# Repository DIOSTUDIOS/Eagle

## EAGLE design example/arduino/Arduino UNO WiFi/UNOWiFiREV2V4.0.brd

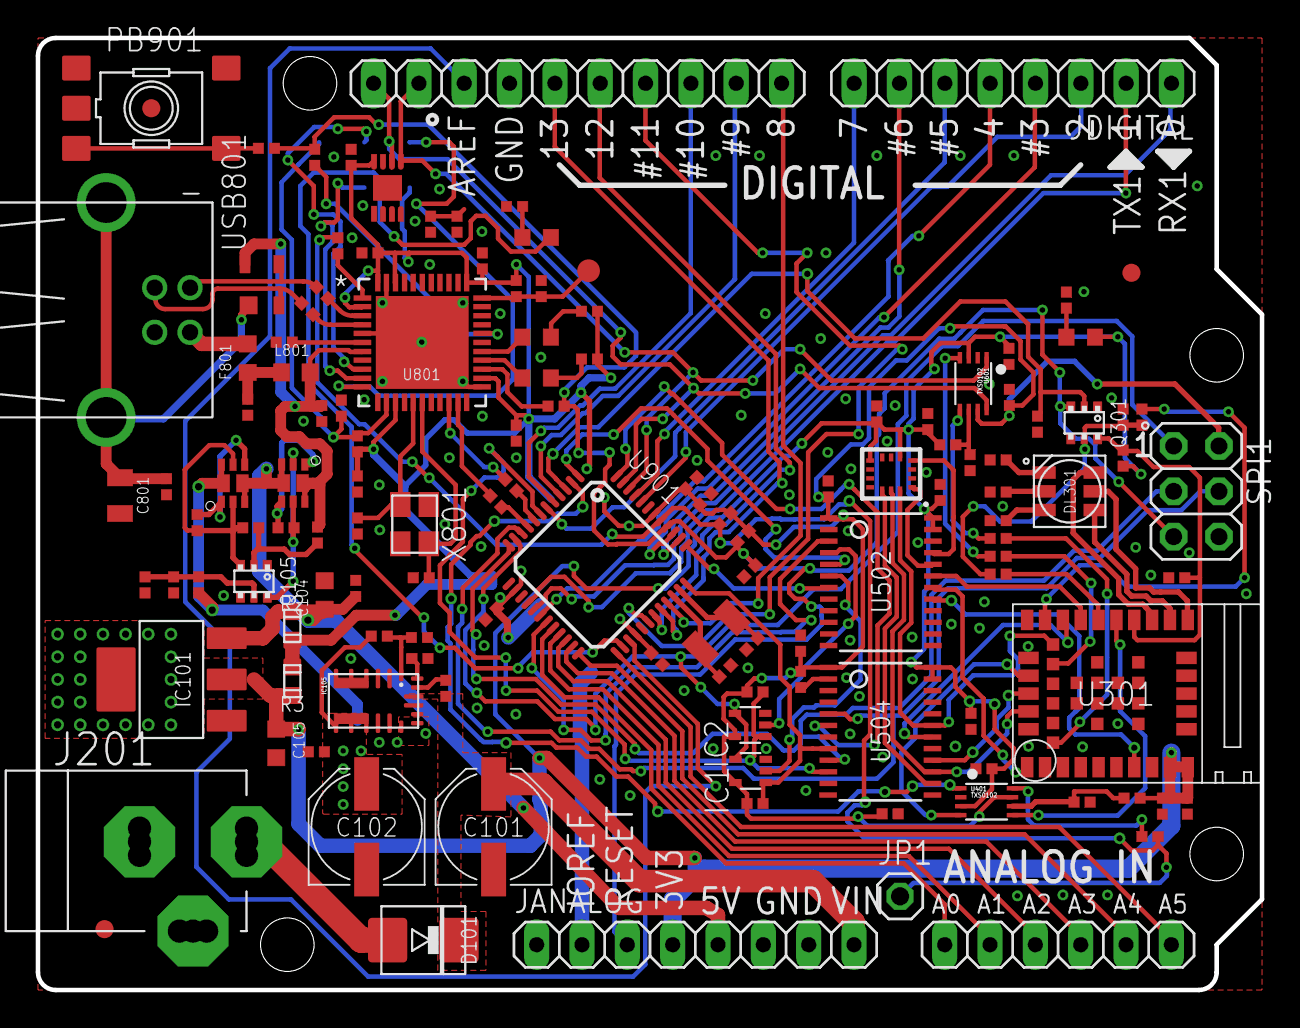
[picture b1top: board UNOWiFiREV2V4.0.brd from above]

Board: 2 copper layers, 68.6 x 53.3 mm, 145 parts (1 on the bottom side), 117 nets.

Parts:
C1, C103, C106, C114, C201, C202, C301, C302, C303, C401, C402, C403, C503, C504, C505, C506, C601, C602, C603, C701, C805, C806, C807, C808, C809, C902, C903, C906, C907: 100n; 0402-1005X55N
C2, C901: 4u7; 0402-1005X55N
C101, C102: 47u; PANASONIC_D
C104, C105: 10u; 0603-1608X90N
C801: 4n7; 0805-R2013X50N
C802, C803: 1n; 0402-1005X55N
C804: 1u; 0402-1005X55N
C810, C811: 12pF; 0402-1005X55N
C904, C905: 20p; 0402-1005X55N
D101: 1N4007; SMB_DO214AA
D801: PRTR5V; SOT190P230X110-4N
DL301: RGB; RGBLED
F801: 0.5A; 0603-1608X90N
FD1, FD2, FD3: DNP; FD-1-2
FRAME1, FRAME101, FRAME201, FRAME301, FRAME401, FRAME501, FRAME601, FRAME701, FRAME801, FRAME901: DNP; FRAME
GND800: DNP; TP-1.00MM
HOLDER: HOLDER-UNOWIFI; HOLDER
IC1, IC2: 74LVC1G125DCKR; SC70-5
IC101: -; SOT223
IC105: MPM3610
J201: -; POWERSUPPLY_DC-21MM
JANALOG: -; 1X14_
JDIGITAL: -; 1X18_
JP1: 1X01
L801: BLM18PG471; 0603-1608X90N
LRX800: YELLOW; LEDC1608X80N-AK
LTX800: YELLOW; LEDC1608X80N-AK
MISO800: DNP; TP-1.00MM
MOSI800: DNP; TP-1.00MM
ON100: GREEN; LEDC1608X80N-AK
PB901: -; TS42
Q101, Q102: DMP2160; PWR_SC70
Q105, Q301: BSS138PS; SOT363
R1, R804, R805, R807, R808: 1k; 0402-1005X55N
R2: 0R; C0603
R3: DNP; C0603
R4, R303, R304, R310, R806: 0R; 0402-1005X55N
R5, R11, R102, R123, R124, R125, R130, R301, R302, R308, R405, R504, R605, R803, R809, R902: 100k; 0402-1005X55N
R101, R126, R305, R306, R307, R802, R903: 330R; 0402-1005X55N
R127, R128: 10k; 0402-1005X55N
R129: 19k1; 0402-1005X55N
R131: 53k6; 0402-1005X55N
R309, R810, R901: DNP; 0402-1005X55N
R801: 1M; 0402-1005X55N
R811, R812: 22R; 0402-1005X55N
R904: 39R; 0402-1005X55N
RST800: DNP; TP-1.00MM
SCK800: DNP; TP-1.00MM
SPI1: -; 2X03
TP801: DNP; TP-1.27MM
U201: LSM6DS3TR; LGA14L
U301: NINA-W132; NINA-W1X
U401, U601: TXS0102; VFSOP-8
U502, U504: MC74LVX4245; TSSOP24
U701: ECC608; SON50P300X200X60-9N-EP160X140
U801: ATMEGA32U4RC; QFN50P700X700X100-45N
U901: ATMEGA4809; TQFP48
USB801: -; USB-B-H
USR: YELLOW; LEDC1608X80N-AK
VDD800: DNP; TP-1.00MM
X801: 16MHz; CRYSTAL-3.2-2.5
Y901: 32768Hz; ABS07

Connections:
2XTRANSLATOR1:N$1: C601.1, R605.1, U601.P$6
2XTRANSLATOR2:N$1: C401.1, R405.1, U401.P$6
16XTRANSLATOR1:N$1: R504.1, U504.2
+3V3: C105.1, C201.1, C202.1, C301.1, C302.2, C402.1, C505.1, C506.1, C602.1, IC101.2, IC101.4, JANALOG.4, ON100.A, R3.1, R301.2, R405.2, R605.2, U201.5, U201.8, U301.9, U301.10, U401.P$3, U502.23, U502.24, U504.23, U504.24, U601.P$3
+5V: C104.1, C106.1, IC101.3, JANALOG.5, Q101.D2, Q101.D2', Q102.D2, Q102.D2', R2.1
GND: C1.2, C2.2, C101.-, C102.-, C103.2, C104.2, C105.2, C106.2, C114.2, C201.2, C202.2, C301.2, C302.1, C303.2, C401.2, C402.2, C403.2, C503.2, C504.2, C505.2, C506.2, C601.2, C602.2, C603.2, C701.1, C801.2, C802.2, C803.2, C804.2, C805.2, C806.2, C807.2, C808.1, C809.1, C810.2, C811.1, C901.2, C902.1, C903.2, C904.2, C905.2, C906.1, C907.1, GND800.X, IC1.3, IC2.3, IC101.1, IC105.3, IC105.12, IC105.13, IC105.14, J201.-1, J201.-2, J201.-3, J201.E1, J201.E2, J201.E3, JANALOG.6, JANALOG.7, JDIGITAL.15, PB901.1, PB901.2, PB901.5, Q105.1, Q105.4, Q301.1, Q301.4, R1.2, R101.2, R124.1, R129.1, R131.1, R302.2, R305.1, R306.1, R307.1, R308.2, R801.1, R810.1, SPI1.6, U201.2, U201.3, U201.6, U201.7, U301.6, U301.12, U301.14, U301.26, U301.30, U301.GND@1, U301.GND@2, U301.GND@3, U301.GND@4, U301.GND@5, U301.GND@6, U301.GND@7, U301.GND@8, U301.GND@9, U301.GND@10, U301.GND@11, U301.GND@12, U401.P$2, U502.2, U502.11, U502.12, U502.13, U502.14, U502.15, U502.16, U502.22, U504.3, U504.4, U504.7, U504.11, U504.12, U504.13, U504.22, U601.P$2, U701.4, U701.9, U801.5, U801.15, U801.23, U801.35, U801.43, U801.45, U901.15, U901.29, U901.43, USB801.GND, X801.2, X801.4
MEDBG1:N$1: C801.1, D801.1, R801.2, USB801.SHIELD1, USB801.SHIELD2
MEDBG1:N$2: F801.2, USB801.VBUS
MEDBG1:N$3: C802.1, F801.1, L801.1
MEDBG1:N$4: R802.1, U801.1
MEDBG1:N$5: C804.1, U801.6
MEDBG1:N$6: C805.1, R803.1, RST800.X, U801.13
MEDBG1:N$7: C811.2, U801.16, X801.1
MEDBG1:N$8: C810.1, U801.17, X801.3
MEDBG1:N$9: R804.2, U801.20
MEDBG1:N$10: R805.2, U801.21
MEDBG1:N$11: LTX800.C, U801.27
MEDBG1:N$12: R806.1, U801.25
MEDBG1:N$13: LRX800.C, U801.26
MEDBG1:N$14: LTX800.A, R808.1
MEDBG1:N$15: LRX800.A, R807.1
MEDBG1:N$16: R809.1, R810.2, TP801.X, U801.33
MEDBG1:N$17: MISO800.X, U801.11
MEDBG1:N$18: MOSI800.X, U801.10
MEDBG1:N$19: SCK800.X, U801.9
MEDBG1:USB2_N: R811.1, U801.3
MEDBG1:USB2_PI: R812.1, U801.4
MEDBG1:USB_N: D801.3, R811.2, USB801.D-
MEDBG1:USB_P: D801.2, R812.2, USB801.D+
unnamed: U301.20, U401.P$5
unnamed: U301.1, U502.18
unnamed: U301.22, U502.19
unnamed: U201.14, U301.36, U504.19
unnamed: U301.23, U504.18
unnamed: U201.1, U502.20
unnamed: U301.27, U401.P$4
unnamed: U301.28, U504.16
unnamed: IC1.2, U502.6
unnamed: IC2.2, U502.4
unnamed: R304.2, U601.P$5
unnamed: R303.2, U601.P$4
unnamed: JP1.1, R4.2, R802.2, R901.1, U901.41
unnamed: U201.4, U502.21
unnamed: U201.12, U504.14
unnamed: R903.2, U801.29
unnamed: U301.7, U502.17
unnamed: R805.1, U901.9
unnamed: R804.1, U901.8
unnamed: U901.26, USR.A
unnamed: R1.1, USR.C
unnamed: U201.13, U301.29, U504.15
PA0: JDIGITAL.3, U901.44
PA1: JDIGITAL.8, U901.45
PA2: JDIGITAL.17, U601.P$1, U701.5, U901.46
PA3: JDIGITAL.18, U601.P$8, U701.6, U901.47
PA4: U504.6, U901.48
PA5: U502.5, U901.1
PA6: U401.P$1, U901.2
PA7: Q301.2, R302.1, U901.3
PB0: JDIGITAL.10, U901.4
PB1: JDIGITAL.11, U901.5
PB2: JDIGITAL.6, U901.6
PB3: IC2.1, R5.1, U504.10, U901.7
PC0: SPI1.4, U504.5, U901.10
PC1: IC1.4, IC2.4, SPI1.1, U901.11
PC2: SPI1.3, U504.9, U901.12
PC4: JDIGITAL.2, U901.16
PC5: JDIGITAL.1, U901.17
PC6: JDIGITAL.5, U901.18
PC7: U502.3, U901.19
PD0: JANALOG.9, U901.20
PD1: JANALOG.10, U901.21
PD2: JANALOG.11, U901.22
PD3: JANALOG.12, U901.23
PD4: JANALOG.13, U901.24
PD5: JANALOG.14, U901.25
PD7: C1.1, C2.1, JDIGITAL.16, U901.27
PE0: JDIGITAL.12, U901.30
PE1: JDIGITAL.13, U901.31
PE2: JDIGITAL.14, U901.32
PE3: JDIGITAL.9, U901.33
PF2: IC1.1, R11.1, U504.8, U901.36
PF3: U502.7, U901.37
PF4: JDIGITAL.7, U901.38
PF5: JDIGITAL.4, U901.39
PWR1:N17690335: Q101.S1, Q101.S2, R127.2
PWR1:N17690346: Q101.G1, Q101.G2, Q105.6, R127.1
PWR1:N17690381: Q105.2, R125.1, R126.2
PWR1:N17690821: Q102.S1, Q102.S2, R128.2
PWR1:N17690840: Q102.G1, Q102.G2, Q105.3, R126.1, R128.1
PWR1:N17690878: C114.1, Q105.5, R123.1, R124.2
PWR1:N$1: D101.A, J201.+1, J201.+2, J201.+3
PWR1:N$3: C102.+, C103.1, IC105.7, IC105.8, IC105.9, IC105.20, Q102.D1, Q102.D1', R102.2, R123.2
PWR1:N$4: ON100.C, R101.1
PWR1:N$35: IC105.1, R102.1, R129.2
PWR1:N$36: IC105.17, R130.2
PWR1:N$37: IC105.18, R131.2
TRG_RST: C903.1, JANALOG.3, Q301.3, R806.2, R902.1, R903.1, R904.1, SPI1.5, U901.40
UC1:N$2: PB901.3, PB901.4, R904.2
UC1:N$3: C905.1, U901.34, Y901.1
UC1:N$4: C904.1, U901.35, Y901.2
UPDI_REMOTE: R4.1, U401.P$8
VDD: C403.1, C503.1, C504.1, C603.1, C701.2, C806.1, C807.1, C808.2, C809.2, C901.1, C902.2, C906.2, C907.2, IC1.5, IC2.5, JANALOG.2, R2.2, R3.2, R5.2, R11.2, R504.2, R803.2, R807.2, R808.2, R809.2, R901.2, R902.2, SPI1.2, U401.P$7, U502.1, U504.1, U601.P$7, U701.8, U801.2, U801.14, U801.24, U801.34, U801.42, U801.44, U901.14, U901.28, U901.42, VDD800.X
VIN: C101.+, D101.C, IC105.16, JANALOG.8, R130.1
VUSB: C803.1, D801.4, L801.2, Q101.D1, Q101.D1', R125.2, U801.7
WIFI/BLE1:N$1: C303.1, Q301.6, R301.1, U301.19
WIFI/BLE1:N$2: R303.1, U301.35
WIFI/BLE1:N$3: R304.1, U301.31
WIFI/BLE1:N$4: DL301.2, U301.16
WIFI/BLE1:N$5: DL301.1, U301.17
WIFI/BLE1:N$6: DL301.3, U301.18
WIFI/BLE1:N$7: DL301.5, R305.2
WIFI/BLE1:N$8: DL301.6, R306.2
WIFI/BLE1:N$9: DL301.4, R307.2
WIFI/BLE1:N$10: R309.2, U301.24
WIFI/BLE1:N$11: Q301.5, R308.1, R309.1, R310.1
WIFI/BLE1:N$12: R310.2, U301.21

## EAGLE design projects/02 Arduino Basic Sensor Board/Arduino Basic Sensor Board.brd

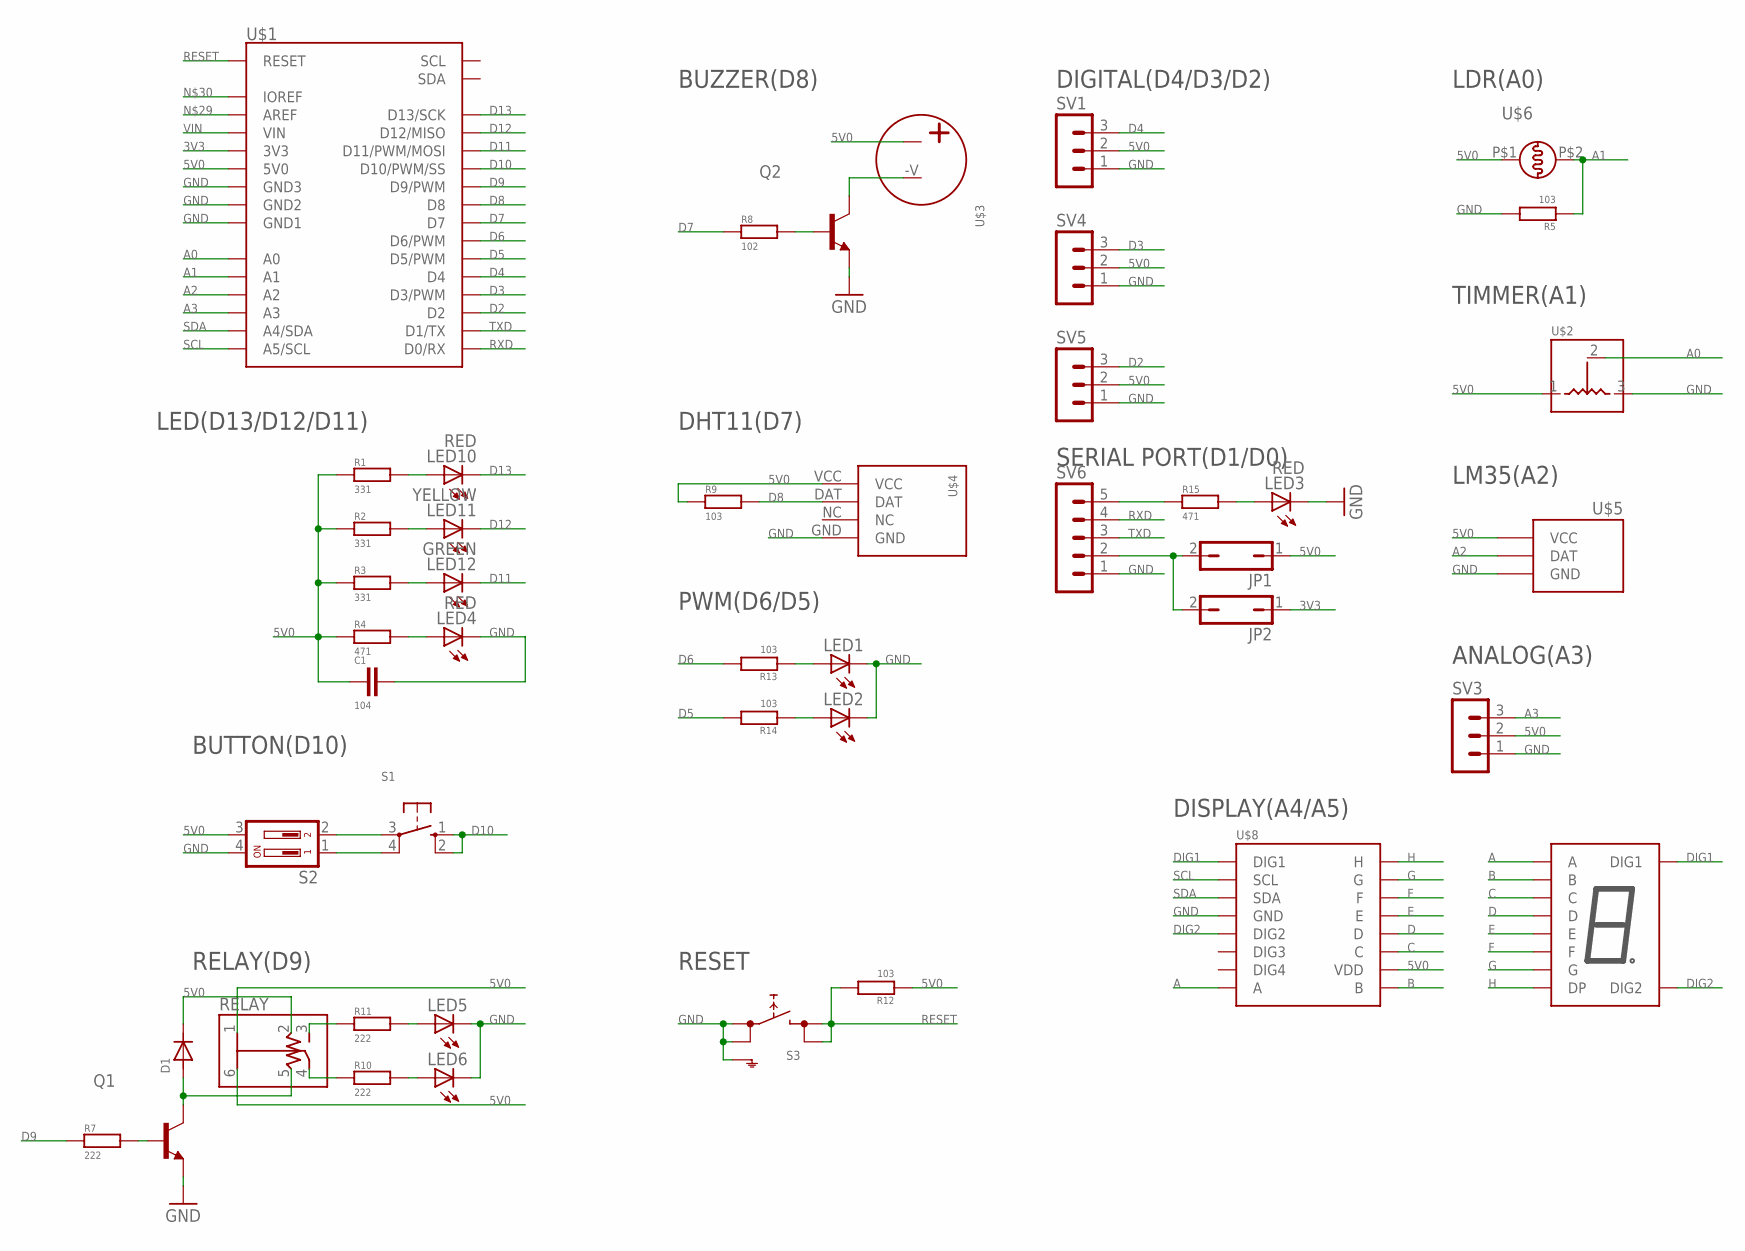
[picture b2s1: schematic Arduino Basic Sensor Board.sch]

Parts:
C1: 104; C0805
D1: DIODESMB; SMB
JP1, JP2: JP1Q
LED1, LED2: LEDCHIPLED_1206; LED1206
LED3, LED4: RED; LED0805
LED5, LED6: LEDSML1206; SML1206
LED10: RED; SML1206
LED11: YELLOW; SML1206
LED12: GREEN; SML1206
Q1, Q2: S8050SOT23; SOT23
R1, R2, R3: 331; R0805
R4, R15: 471; R0805
R5, R9, R12, R13, R14: 103; R0805
R7, R10, R11: 222; R0805
R8: 102; R0805
RELAY: RELAY-HK4100F-DC5V
S1: TS-DIP-4.54.5; TS-DIP-4.5*4.5
S2: SD4-02
S3: TS-SMD_6S6_SHIELD; TS-SMD_6*6_SHIELD
SV1, SV3, SV4, SV5: MA03-1
SV6: MA05-1
U$1: ARDUINO-UNO
U$2: 33623362; 3362
U$3: BUZZER
U$4: DHT11
U$5: LM35; TO92
U$6: LDR
U$8: TM1650; SOP16
U$15: 3261AS; TN_AS_2_0.36INCH

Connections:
3V3: JP2.1, U$1.3V3
5V0: C1.2, D1.1, JP1.1, R1.1, R2.1, R3.1, R4.1, R9.1, R12.1, RELAY.1, RELAY.2, RELAY.6, S2.3, SV1.2, SV3.2, SV4.2, SV5.2, U$1.5V0, U$2.1, U$3.+V, U$4.VCC, U$5.1 (VCC), U$6.P$1, U$8.10 (VDD)
A: U$8.8 (A), U$15.3 (A)
A0: U$1.A0, U$2.2
A1: R5.1, U$1.A1, U$6.P$2
A2: U$1.A2, U$5.2 (DAT)
A3: SV3.3, U$1.A3
B: U$8.9 (B), U$15.9 (B)
C: U$8.11 (C), U$15.8 (C)
D: U$8.12 (D), U$15.6 (D)
D2: SV5.3, U$1.D2
D3: SV4.3, U$1.D3 (D3/PWM)
D4: SV1.3, U$1.D4
D5: R14.2, U$1.D5 (D5/PWM)
D6: R13.2, U$1.D6 (D6/PWM)
D7: R8.1, U$1.D7
D8: R9.2, U$1.D8, U$4.DAT
D9: R7.1, U$1.D9 (D9/PWM)
D10: S1.1 (S), S1.2 (S1), U$1.D10 (D10/PWM/SS)
D11: LED12.C, U$1.D11 (D11/PWM/MOSI)
D12: LED11.C, U$1.D12 (D12/MISO)
D13: LED10.C, U$1.D13 (D13/SCK)
DIG1: U$8.1 (DIG1), U$15.10 (DIG1)
DIG2: U$8.5 (DIG2), U$15.5 (DIG2)
E: U$8.13 (E), U$15.7 (E)
F: U$8.14 (F), U$15.4 (F)
G: U$8.15 (G), U$15.1 (G)
GND: C1.1, LED1.C, LED2.C, LED3.C, LED4.C, LED5.C, LED6.C, Q1.E, Q2.E, R5.2, S2.4, S3.1 (1.1), S3.2 (1.2), S3.5 (SH), SV1.1, SV3.1, SV4.1, SV5.1, SV6.1, U$1.GND1, U$1.GND2, U$1.GND3, U$2.3, U$4.GND, U$5.3 (GND), U$8.4 (GND)
H: U$8.16 (H), U$15.2 (DP)
unnamed: LED10.A, R1.2
unnamed: LED11.A, R2.2
unnamed: LED12.A, R3.2
unnamed: LED4.A, R4.2
unnamed: S1.4 (P1), S2.1
unnamed: S1.3, S2.2
unnamed: LED1.A, R13.1
unnamed: R10.1, RELAY.4
unnamed: R11.1, RELAY.3
unnamed: LED6.A, R10.2
unnamed: LED5.A, R11.2
unnamed: LED2.A, R14.1
unnamed: JP1.2, JP2.2, SV6.2
unnamed: R15.1, SV6.5
unnamed: LED3.A, R15.2
unnamed: D1.2, Q1.C, RELAY.5
unnamed: Q1.B, R7.2
unnamed: Q2.B, R8.2
unnamed: Q2.C, U$3.-V
RESET: R12.2, S3.3 (2.1), S3.4 (2.2), U$1.RST (RESET)
RXD: SV6.4, U$1.D0 (D0/RX)
SCL: U$1.A5 (A5/SCL), U$8.2 (SCL)
SDA: U$1.A4 (A4/SDA), U$8.3 (SDA)
TXD: SV6.3, U$1.D1 (D1/TX)
VIN: U$1.VIN

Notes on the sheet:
LED(D13/D12/D11)
BUTTON(D10)
RELAY(D9)
SERIAL PORT(D1/D0)
DHT11(D7)
BUZZER(D8)
ANALOG(A3)
LM35(A2)
TIMMER(A1)
LDR(A0)
PWM(D6/D5)
DIGITAL(D4/D3/D2)
RESET
DISPLAY(A4/A5)

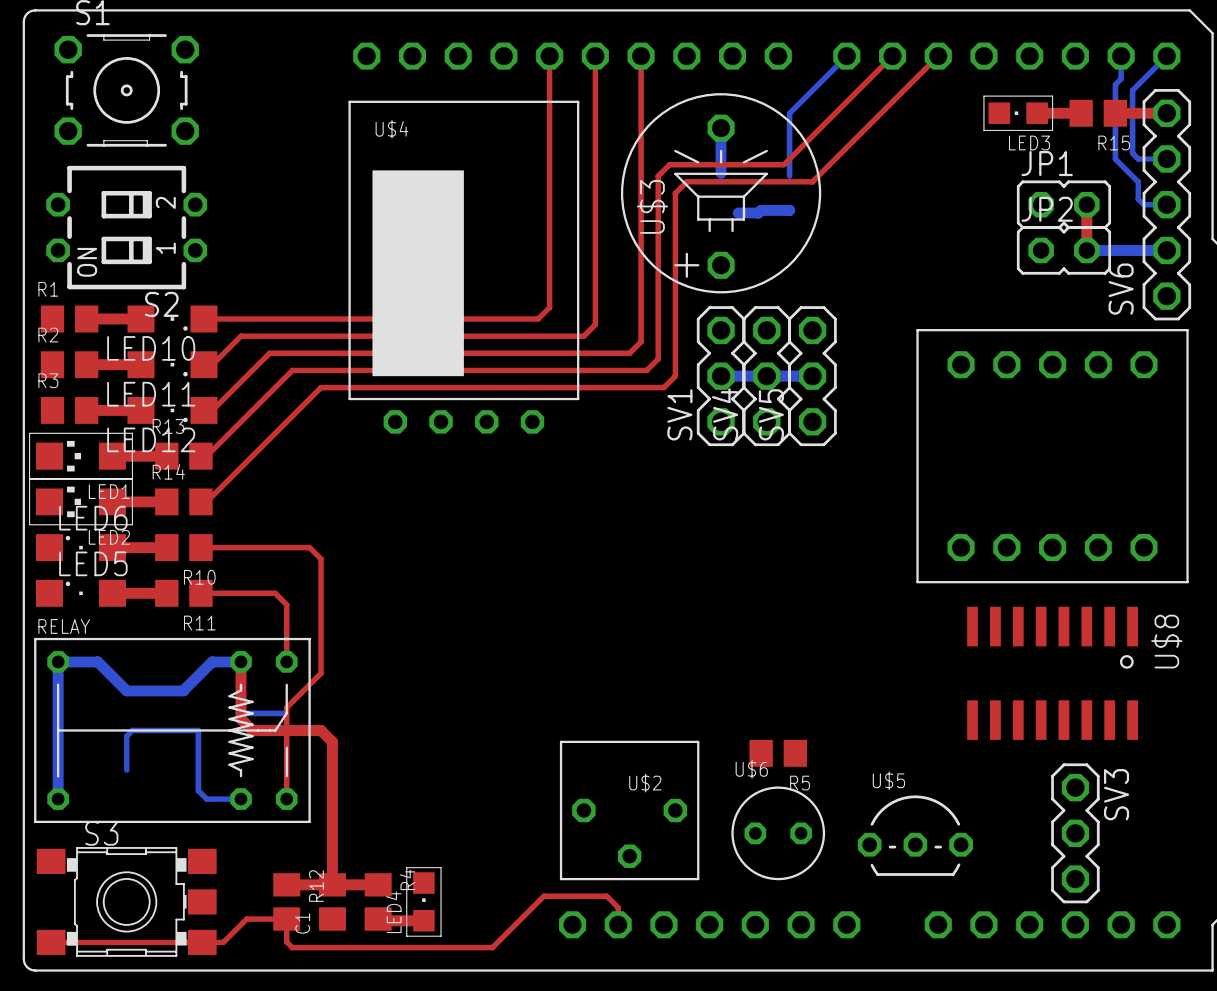
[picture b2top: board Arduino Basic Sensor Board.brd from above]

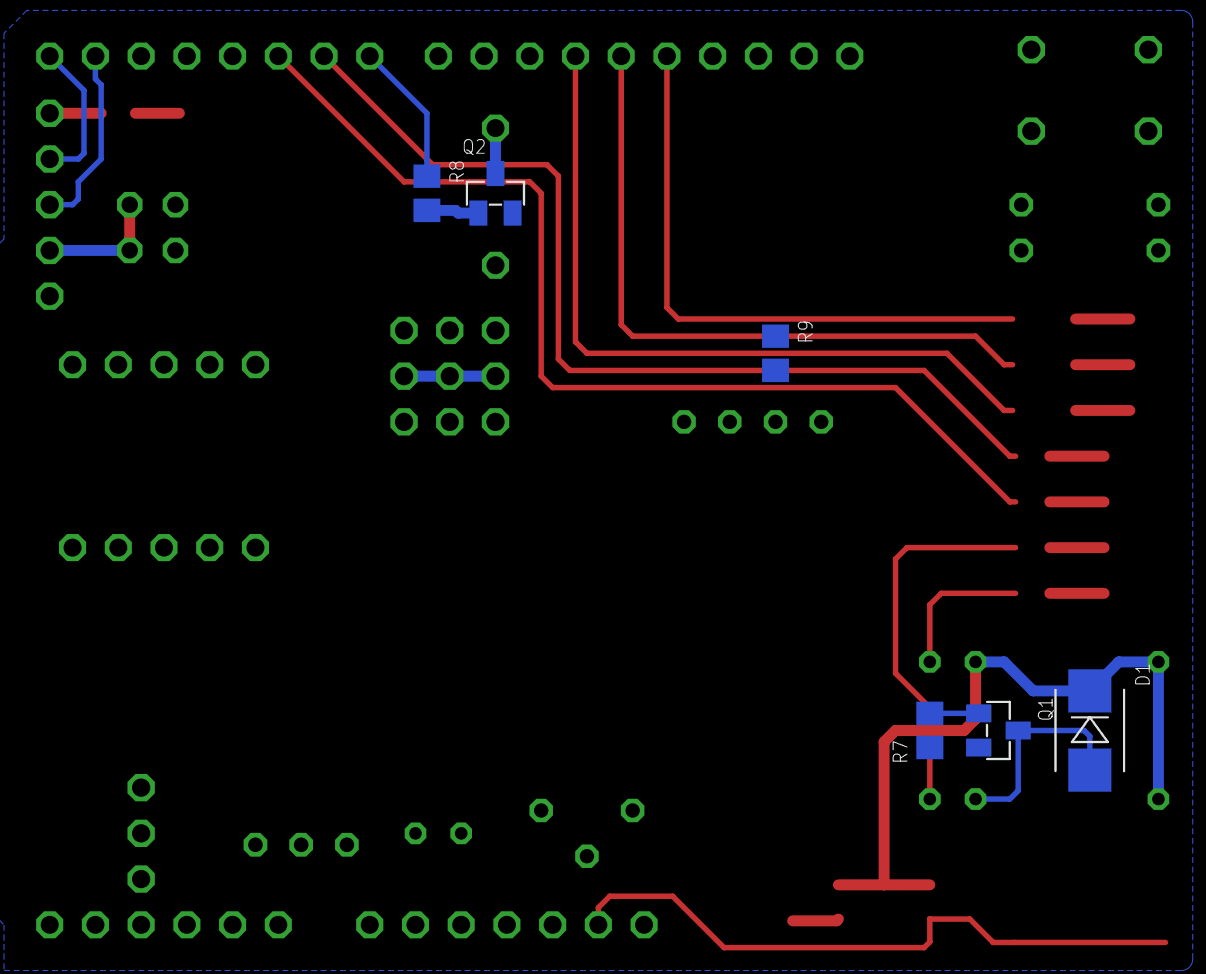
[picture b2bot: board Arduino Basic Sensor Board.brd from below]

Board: 2 copper layers, 46 parts (6 on the bottom side), 53 nets.

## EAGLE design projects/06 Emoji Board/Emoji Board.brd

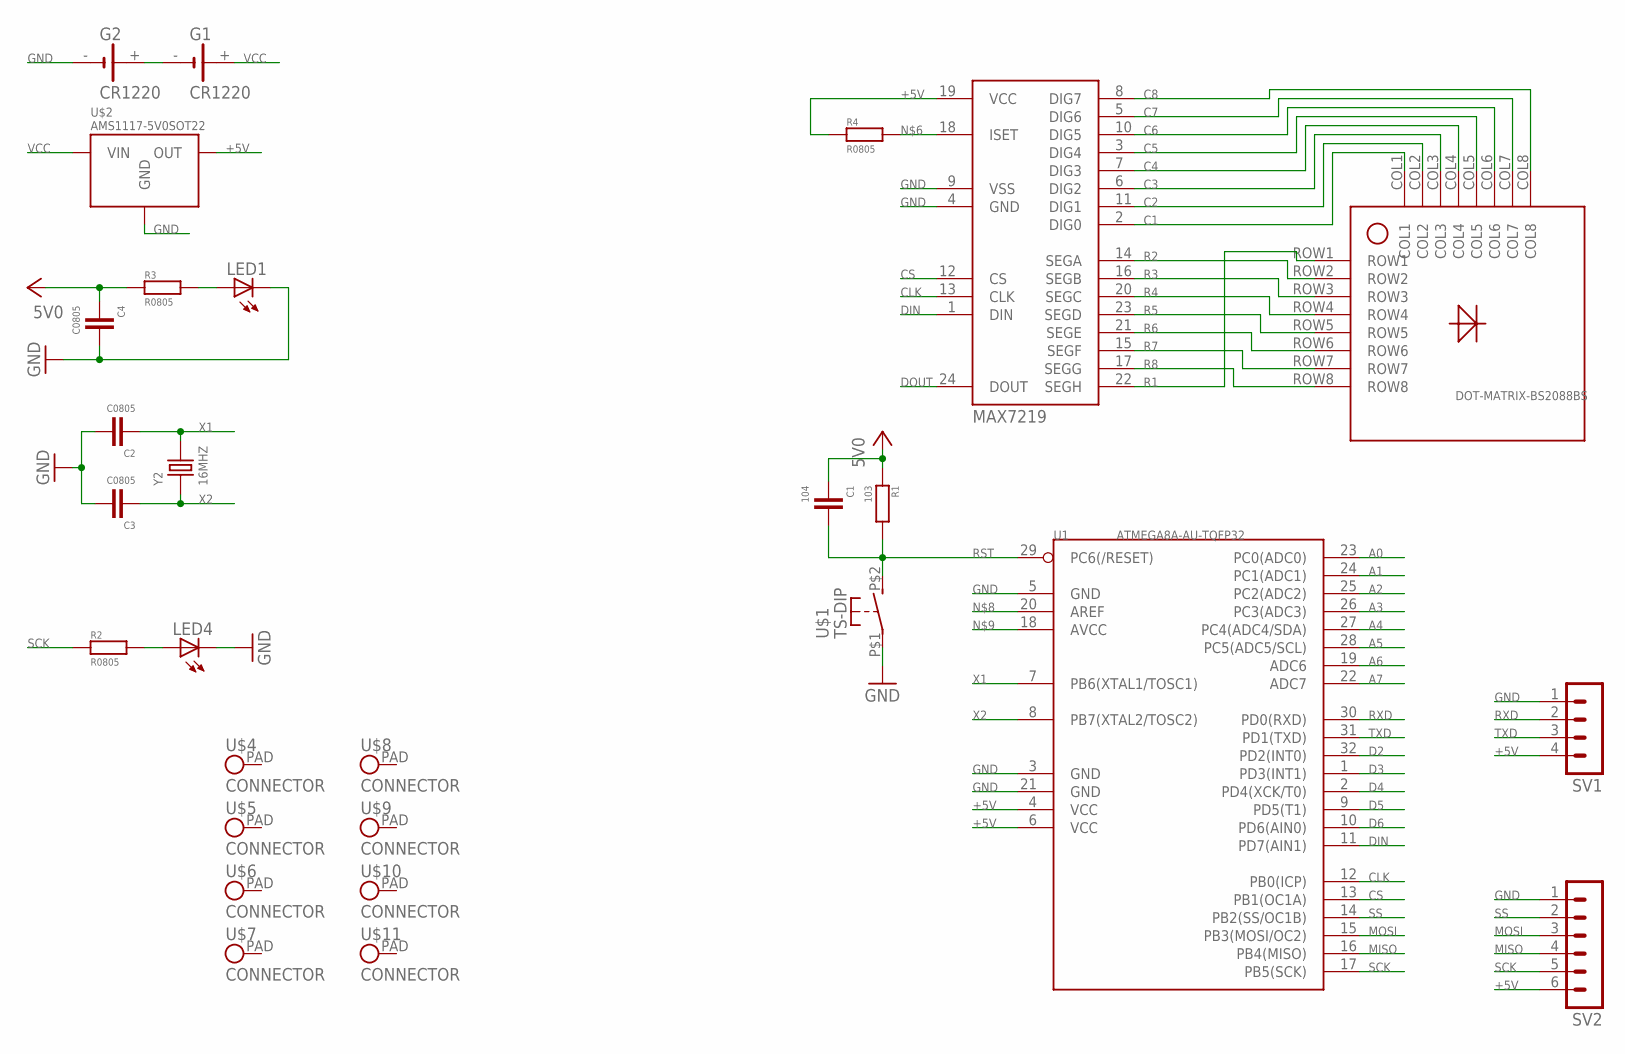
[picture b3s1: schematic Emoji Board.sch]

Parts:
C1: 104; C0805
C2, C3, C4: C0805
G1, G2: CR1220
LED1, LED4: LEDSML0805; SML0805
R1: 103; R0805
R2, R3, R4: R0805
SV1: MA04-1
SV2: MA06-1
U1: ATMEGA8A-AU-TQFP32; TQFP32
U$1: TS-DIP
U$2: AMS1117-5V0SOT22; SOT223
U$3: DOT-MATRIX-BS2088BS; 2088BS
U$4, U$5, U$6, U$7, U$8, U$9, U$10, U$11: CONNECTOR; PAD
U$12: MAX7219; SOP24
Y2: 16MHZ; HC49US

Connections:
+5V: C1.2, C4.2, R1.1, R3.1, R4.1, SV1.4, SV2.6, U1.4 (VCC), U1.6 (VCC), U$2.OUT, U$12.19 (VCC)
A0: U1.23 (PC0(ADC0))
A1: U1.24 (PC1(ADC1))
A2: U1.25 (PC2(ADC2))
A3: U1.26 (PC3(ADC3))
A4: U1.27 (PC4(ADC4/SDA))
A5: U1.28 (PC5(ADC5/SCL))
A6: U1.19 (ADC6)
A7: U1.22 (ADC7)
C1: U$3.COL1, U$12.2 (DIG0)
C2: U$3.COL2, U$12.11 (DIG1)
C3: U$3.COL3, U$12.6 (DIG2)
C4: U$3.COL4, U$12.7 (DIG3)
C5: U$3.COL5, U$12.3 (DIG4)
C6: U$3.COL6, U$12.10 (DIG5)
C7: U$3.COL7, U$12.5 (DIG6)
C8: U$3.COL8, U$12.8 (DIG7)
CLK: U1.12 (PB0(ICP)), U$12.13 (CLK)
CS: U1.13 (PB1(OC1A)), U$12.12 (CS)
D2: U1.32 (PD2(INT0))
D3: U1.1 (PD3(INT1))
D4: U1.2 (PD4(XCK/T0))
D5: U1.9 (PD5(T1))
D6: U1.10 (PD6(AIN0))
DIN: U1.11 (PD7(AIN1)), U$12.1 (DIN)
DOUT: U$12.24 (DOUT)
GND: C2.1, C3.1, C4.1, G2.-, LED1.C, LED4.C, SV1.1, SV2.1, U1.3 (GND), U1.5 (GND), U1.21 (GND), U$1.P$1, U$2.GND, U$12.4 (GND), U$12.9 (VSS)
MISO: SV2.4, U1.16 (PB4(MISO))
MOSI: SV2.3, U1.15 (PB3(MOSI/OC2))
unnamed: LED4.A, R2.2
unnamed: G1.-, G2.+
unnamed: R4.2, U$12.18 (ISET)
unnamed: LED1.A, R3.2
R1: U$3.ROW1, U$12.22 (SEGH)
R2: U$3.ROW2, U$12.14 (SEGA)
R3: U$3.ROW3, U$12.16 (SEGB)
R4: U$3.ROW4, U$12.20 (SEGC)
R5: U$3.ROW5, U$12.23 (SEGD)
R6: U$3.ROW6, U$12.21 (SEGE)
R7: U$3.ROW7, U$12.15 (SEGF)
R8: U$3.ROW8, U$12.17 (SEGG)
RST: C1.1, R1.2, U1.29 (PC6(/RESET)), U$1.P$2 (S)
RXD: SV1.2, U1.30 (PD0(RXD))
SCK: R2.1, SV2.5, U1.17 (PB5(SCK))
SS: SV2.2, U1.14 (PB2(SS/OC1B))
TXD: SV1.3, U1.31 (PD1(TXD))
VCC: G1.+, U$2.VIN
X1: C2.2, U1.7 (PB6(XTAL1/TOSC1)), Y2.2
X2: C3.2, U1.8 (PB7(XTAL2/TOSC2)), Y2.1

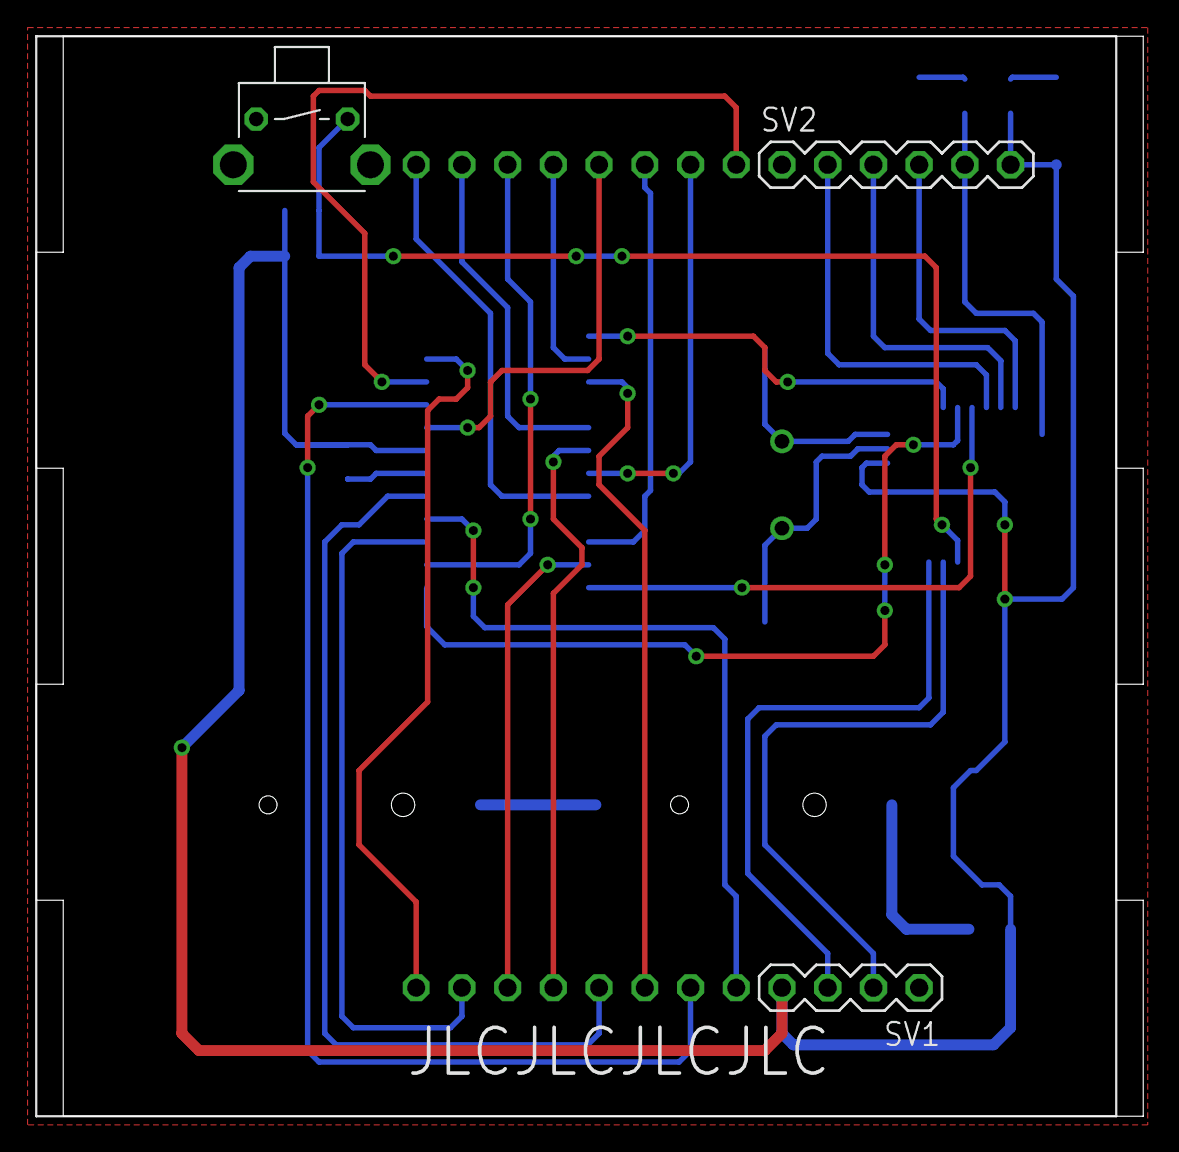
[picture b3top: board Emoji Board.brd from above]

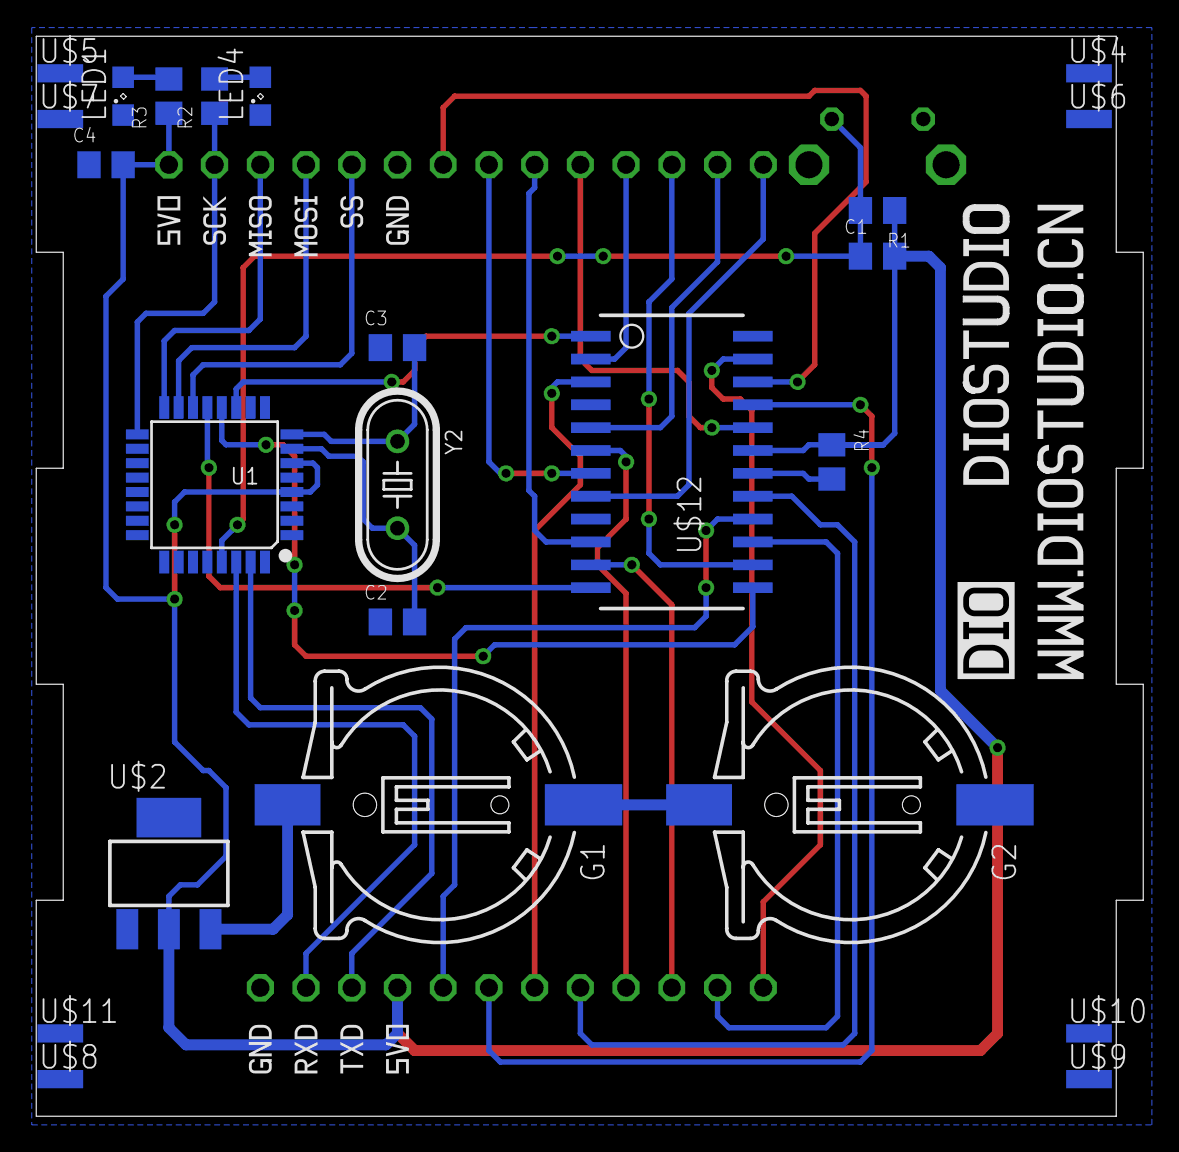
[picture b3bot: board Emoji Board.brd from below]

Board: 2 copper layers, 61.5 x 60.0 mm, 41 parts (37 on the bottom side), 35 nets.

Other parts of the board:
U$13, U$17: 5V0_050
U$14, U$18: GND_050
U$15: TXD_050
U$16: RXD_050
U$20: WWW.DIOSTUDIO.CN_100
U$21: LOGO_100
U$22: DIOSTUDIO_100
U$23: SCK_050
U$24: MISO_050
U$25: MOSI_050
U$26: SS_050

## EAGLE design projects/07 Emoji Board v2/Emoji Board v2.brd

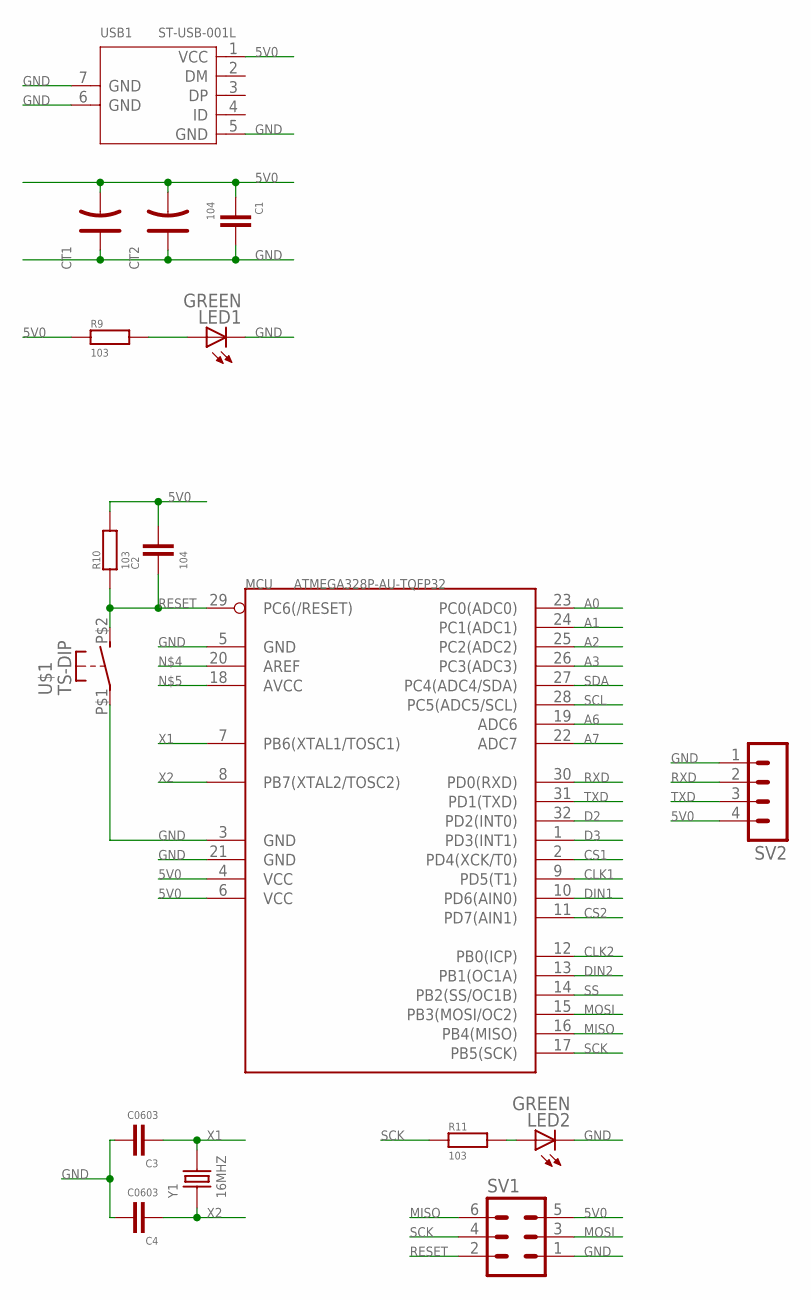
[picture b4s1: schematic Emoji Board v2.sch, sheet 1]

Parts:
C1, C2: 104; C0805
C3, C4: C0603
CT1, CT2: ALUMINUM-SMD-100UF-50V(D6.0-H6.0MM); ELECTRO-SMD-C-6.0MM
LED1, LED2: GREEN; LED0805
MCU: ATMEGA328P-AU-TQFP32; TQFP32
R9, R10, R11: 103; R0805
SV1: MA03-2
SV2: MA04-1
U$1: TS-DIP
USB1: ST-USB-001L; MICRO-USB-SMD-5+2
Y1: 16MHZ; HC49US

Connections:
5V0: C1.2, C2.1, CT1.-, CT2.-, MCU.4 (VCC), MCU.6 (VCC), R9.1, R10.2, SV1.5, SV2.4, USB1.1 (VCC); also elsewhere on the board
A0: MCU.23 (PC0(ADC0))
A1: MCU.24 (PC1(ADC1))
A2: MCU.25 (PC2(ADC2))
A3: MCU.26 (PC3(ADC3))
A6: MCU.19 (ADC6)
A7: MCU.22 (ADC7)
CLK1: MCU.9 (PD5(T1)); also elsewhere on the board
CLK2: MCU.12 (PB0(ICP)); also elsewhere on the board
CS1: MCU.2 (PD4(XCK/T0)); also elsewhere on the board
CS2: MCU.11 (PD7(AIN1)); also elsewhere on the board
D2: MCU.32 (PD2(INT0))
D3: MCU.1 (PD3(INT1))
DIN1: MCU.10 (PD6(AIN0)); also elsewhere on the board
DIN2: MCU.13 (PB1(OC1A)); also elsewhere on the board
GND: C1.1, C3.1, C4.1, CT1.+, CT2.+, LED1.C, LED2.C, MCU.3 (GND), MCU.5 (GND), MCU.21 (GND), SV1.1, SV2.1, U$1.P$1, USB1.5 (GND), USB1.6 (GND), USB1.7 (GND); also elsewhere on the board
MISO: MCU.16 (PB4(MISO)), SV1.6
MOSI: MCU.15 (PB3(MOSI/OC2)), SV1.3
unnamed: LED1.A, R9.2
unnamed: LED2.A, R11.2
RESET: C2.2, MCU.29 (PC6(/RESET)), R10.1, SV1.2, U$1.P$2 (S)
RXD: MCU.30 (PD0(RXD)), SV2.2
SCK: MCU.17 (PB5(SCK)), R11.1, SV1.4
SCL: MCU.28 (PC5(ADC5/SCL))
SDA: MCU.27 (PC4(ADC4/SDA))
SS: MCU.14 (PB2(SS/OC1B))
TXD: MCU.31 (PD1(TXD)), SV2.3
X1: C3.2, MCU.7 (PB6(XTAL1/TOSC1)), Y1.2
X2: C4.2, MCU.8 (PB7(XTAL2/TOSC2)), Y1.1

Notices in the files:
example/arduino/Arduino UNO WiFi/UNOWiFiREV2V4.0.brd:
Copyright (c) 2016-2017 Arduino LLC.  All right reserved. EAGLE Design Rules
parts and their libraries:
Arduino-utility: Copyright (c) 2016-2017 Arduino LLC.  All right reserved.
Arduino-utility: This work is licensed under a Creative Commons Attribution-ShareAlike 4.0 International License.
